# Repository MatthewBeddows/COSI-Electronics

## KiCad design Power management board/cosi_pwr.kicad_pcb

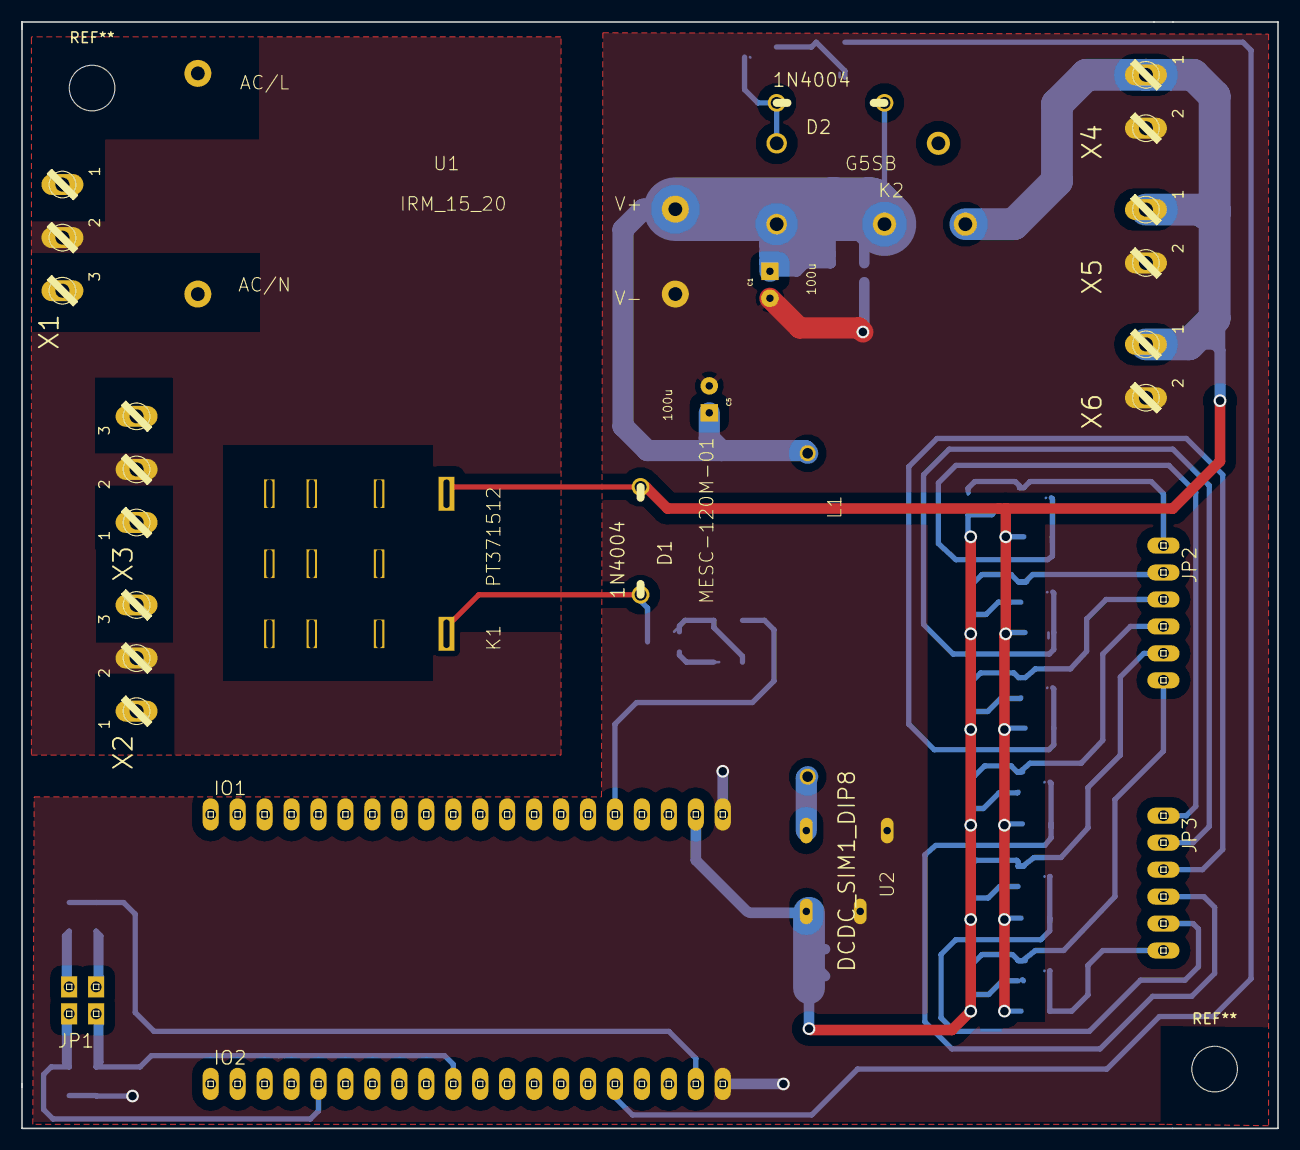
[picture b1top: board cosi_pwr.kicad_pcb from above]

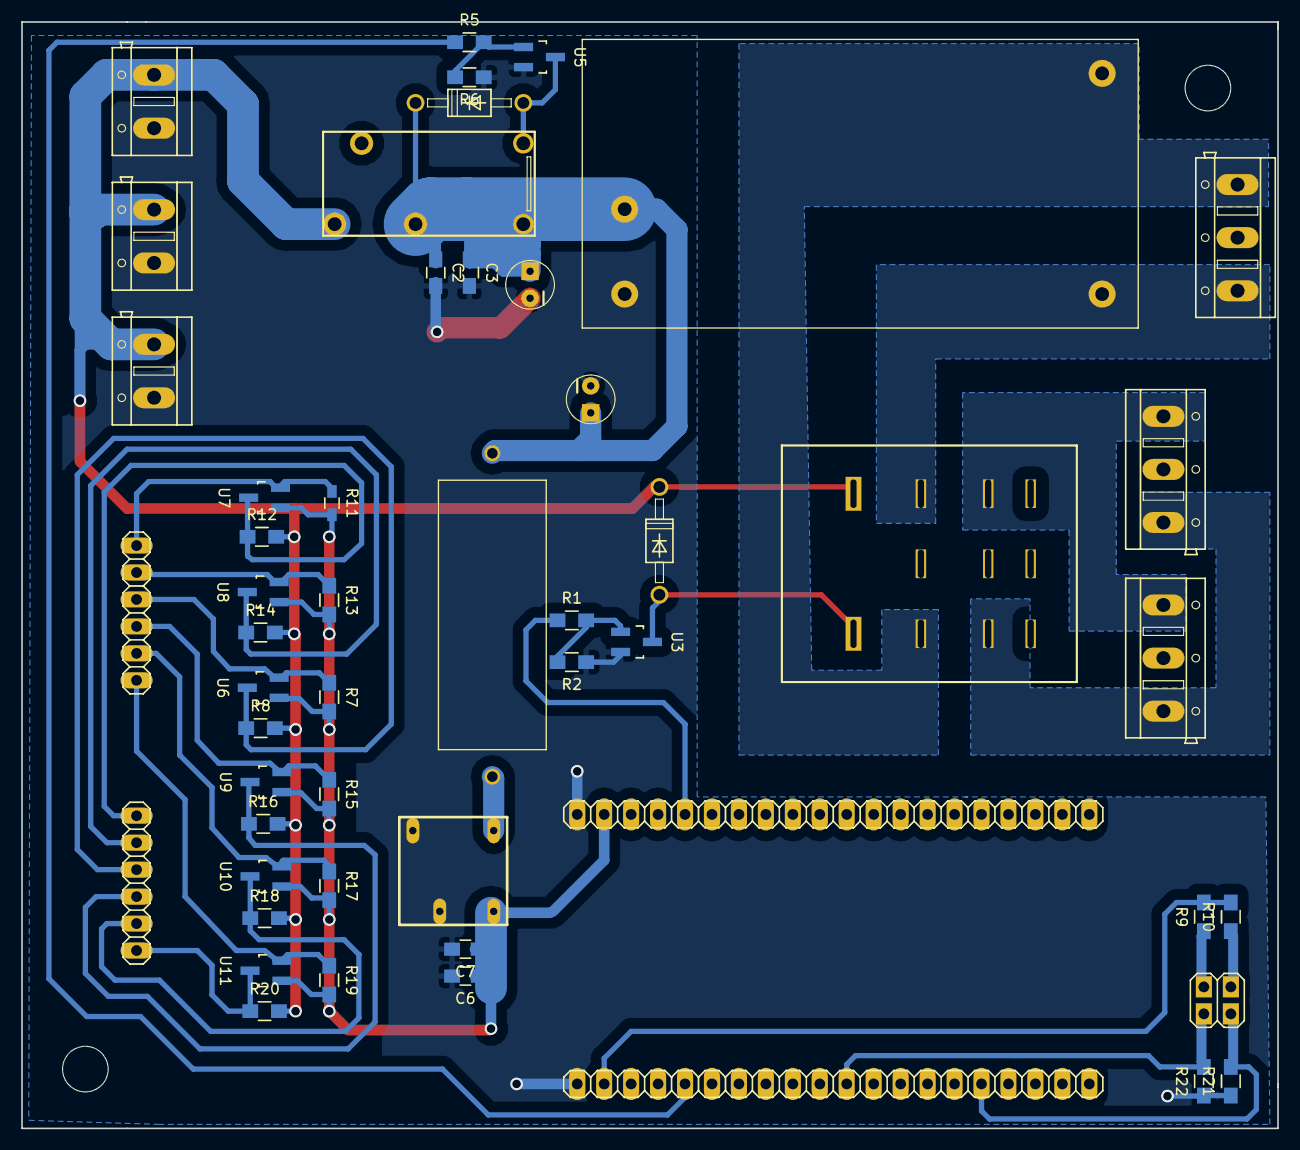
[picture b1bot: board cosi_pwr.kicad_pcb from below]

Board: 2 copper layers, 118.4 x 104.3 mm, 52 parts (32 on the bottom side), 33 nets.

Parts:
C1, C5: 100u; CPOL-RADIAL-100UF-25V
C2, C6: 4.7u; C_0805_HandSoldering
C3, C7: 0.1u; C_0805_HandSoldering
D1, D2: 1N4004; DO41-10
IO1, IO2: 1X20
JP1: 2X02
JP2, JP3: 1X06
K1: PT371512; PT-3
K2: G5SB
L1: MESC-120M-01
R1, R5, R9, R10: 1k; R_0805_HandSoldering
R2, R6, R7, R8, R12, R13, R14, R15, R16, R17, R18, R19, R20, R21, R22: 10k; R_0805_HandSoldering
R11: 10k; R_0603_HandSoldering
U1: IRM_15_20
U2: DCDC_SIM1_DIP8
U3, U5, U6, U7, U8, U9, U10, U11: N-CHANNEL-MOSFET-BSS138; SOT-23_Handsoldering
X1, X2, X3: AK500_3
X4, X5, X6: AK500_2

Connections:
+3V3: IO2.19, R9.2, R10.2
+5V: C6.1, C7.1, IO1.19, R7.2, R11.2, R13.2, R15.2, R17.2, R19.2, U2.5, U6.1, U7.1, U8.1, U9.1, U10.1, U11.1
+12V: C1.1, C2.1, C3.1, C5.1, D2.C, K2.1, K2.2, L1.P$1, U1.V+
/AC_L: K1.31, U1.AC/L, X1.1
/AC_N: K1.11, U1.AC/N, X1.3
/BANK1_4: IO2.5, JP1.4, R21.2
/BANK1_9: IO2.10, JP1.2, R22.2
/BANK1_15: IO2.16, R5.1
/BANK2_15: IO1.16, R1.1
/N$1: R1.2, R2.2, U3.1
/N$2: D1.A, K1.A2, U3.3
/N$4: L1.P$2, U2.4
/N$14: R5.2, R6.2, U5.1
/N$15: D2.A, K2.5, U5.3
/N$19: JP1.1, R9.1
/N$20: JP1.3, R10.1
/SW_X+_H: JP3.1, R12.1, U7.3
/SW_X+_L: JP2.1, R11.1, U7.2
/SW_X-_H: JP3.2, R14.1, U8.3
/SW_X-_L: JP2.2, R13.1, U8.2
/SW_Y+_H: JP3.3, R8.1, U6.3
/SW_Y+_L: JP2.3, R7.1, U6.2
/SW_Y-_H: JP3.4, R16.1, U9.3
/SW_Y-_L: JP2.4, R15.1, U9.2
/SW_Z+_H: JP3.5, R18.1, U10.3
/SW_Z+_L: JP2.5, R17.1, U10.2
/SW_Z-_H: JP3.6, R20.1, U11.3
/SW_Z-_L: JP2.6, R19.1, U11.2
GND: C1.2, C2.2, C3.2, C5.2, C6.2, C7.2, IO1.20, IO2.20, R2.1, R6.1, R21.1, R22.1, U1.V-, U2.1, U2.7, U3.2, U5.2, X4.2, X5.2, X6.2
unnamed: K1.14, X2.3, X3.3
unnamed: K1.34, X2.1, X3.1
PE: X1.2, X2.2, X3.2
VCC_+12V: D1.C, K1.A1, K2.3, R8.2, R12.2, R14.2, R16.2, R18.2, R20.2, X4.1, X5.1, X6.1

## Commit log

2024-10-09 Initialising the repo
    Direct copy from the initial COSI repo
2024-10-09 Copied the content of the assembly instructions
    Using version 1.0 of the COSI system as it is the one we ordered.
2024-10-09 Adding project info
2024-10-09 Fixing the menu items on main page
2024-10-09 Fixing BOMs and tables
2024-10-09 Create LICENSE
2024-12-02 Added module_infor
2025-01-15 modifications of assembly instructions
2025-01-15 Adding info for electronics and casing design
2025-09-08 Added test RA
    Test Risk assessment added.
2025-09-12 Added test BOM
